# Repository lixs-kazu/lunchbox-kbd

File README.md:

# lunchbox-kbd　egg52で不満だった部分を変更したキーボード

具体的には

・使用頻度が極めて低かったため、小指の外側の一列を削除

・できるだけ指の移動量がを減らすため、縦のキーピッチを１８mmに変更。そのため通常のキーキャップは使用できない可能性がある（キーキャップを削る事によって使用可能）chocスイッチの場合問題なく使用できる。

・親指を使用した入力時、他のキーに手が当たるのを防ぐ為に親指部分の角度を変更。

・親指部分の４キーを内側に２mm移動。

・人差し指部分のキーが押しにくかったため、中指から6.5mmの差をつけた。

・小指部分のキーも同様だったので、中指から20mmの差をつけた。

・アクリル箱組ケース制作するときに可能な限りサイドパネルの枚数を減らしたいので、外形を五角形とした。

・ケーブル横出しは狭いスペースで作業するときに邪魔になるので上側にケーブルがでるように変更。

・LEDとOLEDに対応。

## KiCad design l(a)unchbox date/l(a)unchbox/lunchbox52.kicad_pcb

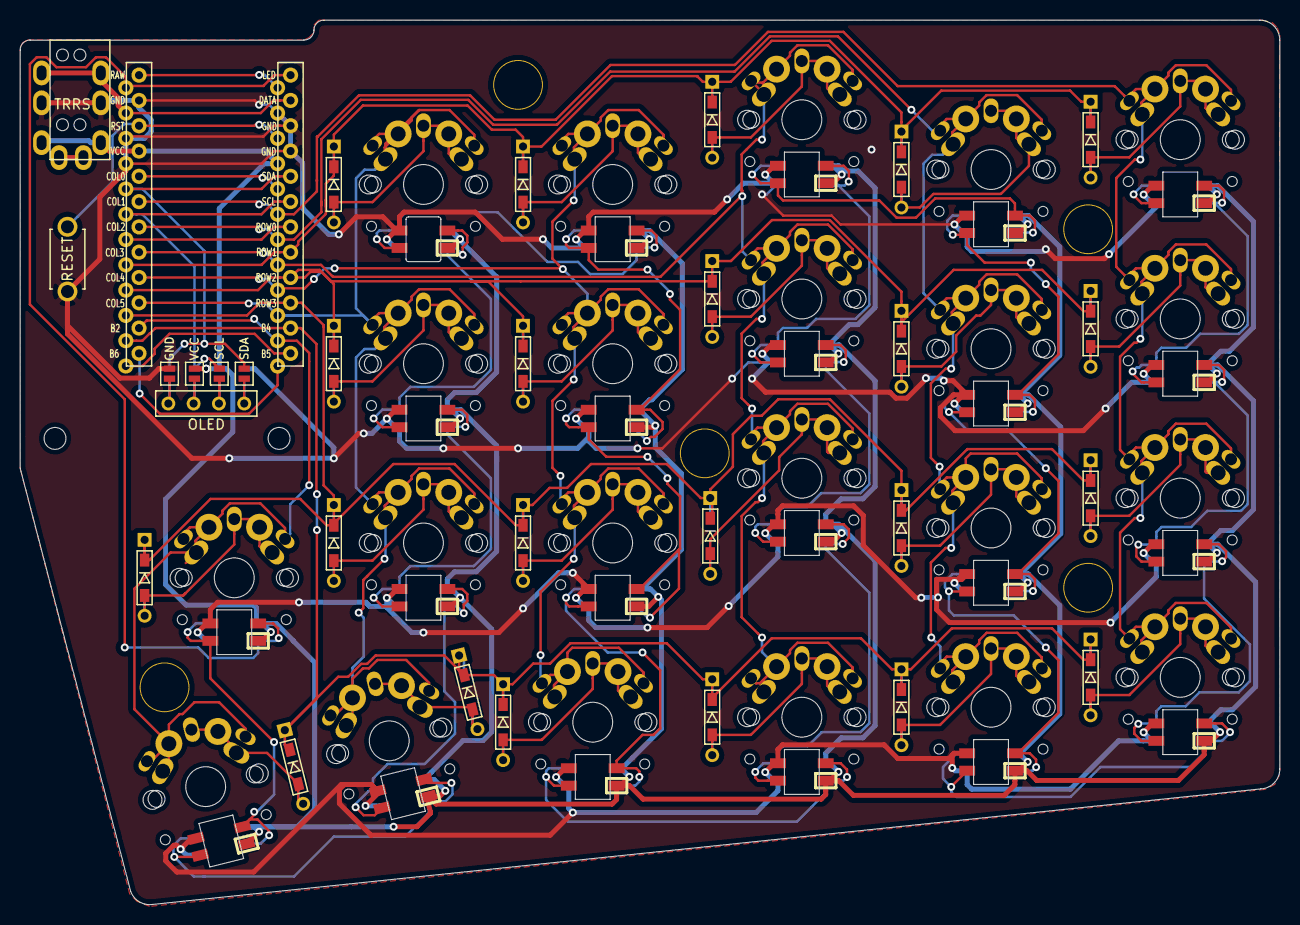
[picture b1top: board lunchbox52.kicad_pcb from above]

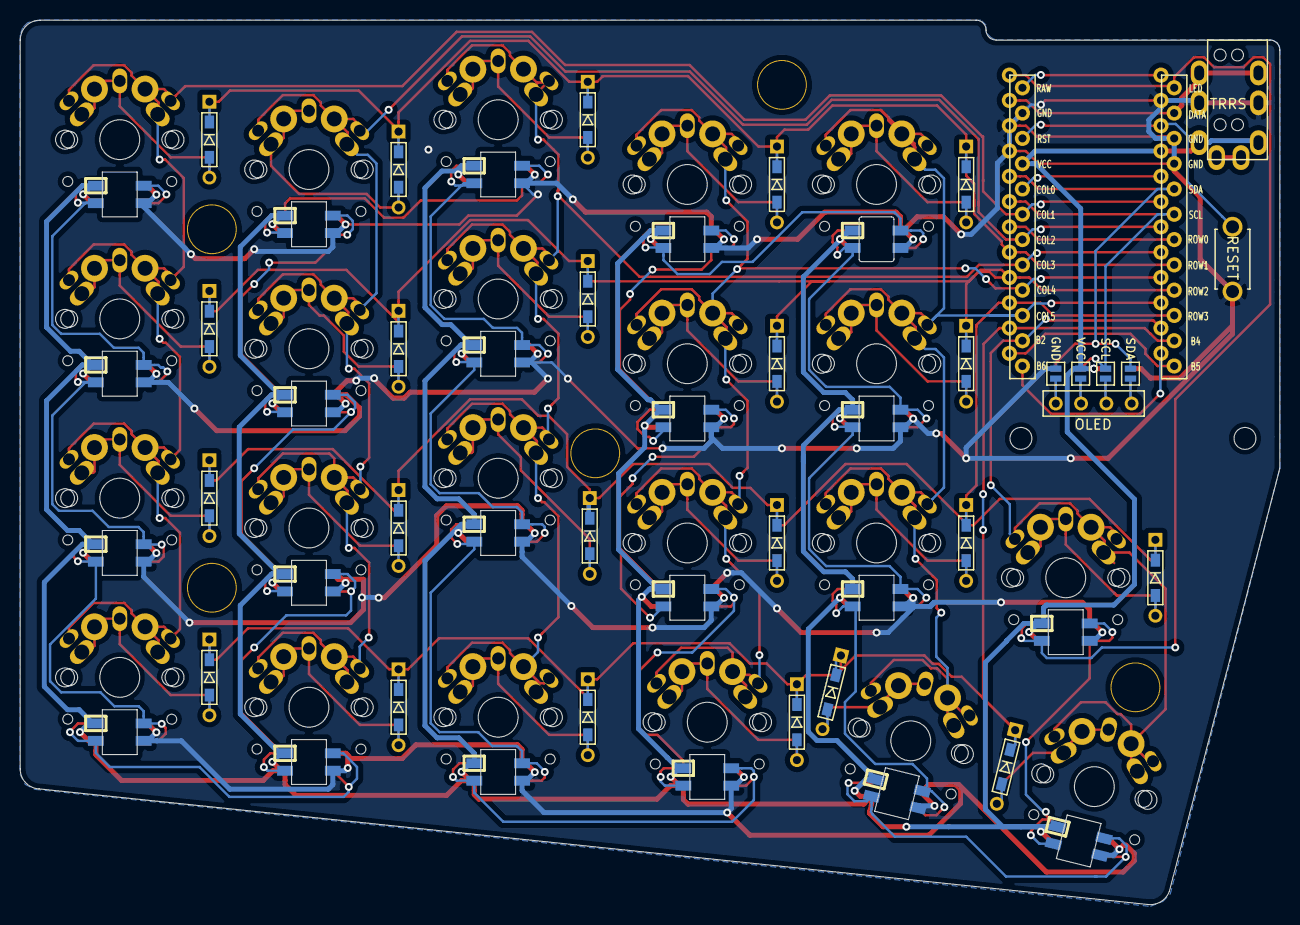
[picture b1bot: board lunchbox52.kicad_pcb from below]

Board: 2 copper layers, 126.5 x 88.8 mm, 83 parts (4 on the bottom side), 64 nets.

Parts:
D1, D2, D3, D4, D5, D6, D7, D8, D9, D10, D11, D12, D13, D14, D15, D16, D17, D18, D19, D20, D21, D22: D; D3_TH_SMD
J1: MJ-4PP-9
J2: Conn_01x04_Female; OLED
JP1, JP8: GND; Jumper
JP2, JP7: VCC; Jumper
JP3, JP6: SCL; Jumper
JP4, JP5: SDA; Jumper
L1, L2, L3, L4, L5, L6, L7, L8, L9, L10, L11, L12, L13, L14, L15, L16, L17, L18, L19, L20, L21, L22: SK6812MINI; SK6812MINI_rev
Ref**: Val**; HOLE
Ref**#2, Ref**#3, Ref**#4, Ref**#5: Val**; HOLE
SW1: SW_PUSH; ResetSW
SW2, SW3, SW4, SW5, SW6, SW7, SW8, SW9, SW10, SW11, SW12, SW13, SW14, SW15, SW16, SW17, SW18, SW19, SW20, SW21, SW22, SW23: SW_Push; MX_PG1350_FLIP_HOLES
U1: ProMicro; ProMicro_v2

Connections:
GND: J1.C, JP1.2, JP8.2, L1.2, L2.2, L3.2, L4.2, L5.2, L6.2, L7.2, L8.2, L9.2, L10.2, L11.2, L12.2, L13.2, L14.2, L15.2, L16.2, L17.2, L18.2, L19.2, L20.2, L21.2, L22.2, SW1.2, U1.3, U1.4, U1.23
LED: L1.3, U1.1
unnamed: D1.2, SW2.2
unnamed: D2.2, SW3.2
unnamed: D3.2, SW4.2
unnamed: D4.2, SW5.2
unnamed: D5.2, SW6.2
unnamed: D6.2, SW7.2
unnamed: D7.2, SW8.2
unnamed: D8.2, SW9.2
unnamed: D9.2, SW10.2
unnamed: D10.2, SW11.2
unnamed: D11.2, SW12.2
unnamed: D12.2, SW13.2
unnamed: D13.2, SW14.2
unnamed: D14.2, SW15.2
unnamed: D15.2, SW16.2
unnamed: D16.2, SW17.2
unnamed: D17.2, SW18.2
unnamed: D18.2, SW19.2
unnamed: D19.2, SW20.2
unnamed: D20.2, SW21.2
unnamed: D21.2, SW22.2
unnamed: D22.2, SW23.2
unnamed: J2.1, JP4.1, JP8.1
unnamed: J2.2, JP3.1, JP7.1
unnamed: J2.3, JP2.1, JP6.1
unnamed: J2.4, JP1.1, JP5.1
unnamed: L1.1, L2.3
unnamed: L2.1, L6.3
unnamed: L3.1, L7.3
unnamed: L3.3, L4.1
unnamed: L4.3, L5.1
unnamed: L5.3, L6.1
unnamed: L7.1, L8.3
unnamed: L8.1, L9.3
unnamed: L10.1, L14.3
unnamed: L9.1, L10.3
unnamed: L11.1, L15.3
unnamed: L11.3, L12.1
unnamed: L12.3, L13.1
unnamed: L13.3, L14.1
unnamed: L15.1, L16.3
unnamed: L16.1, L17.3
unnamed: L17.1, L18.3
unnamed: L18.1, L22.3
unnamed: L19.3, L20.1
unnamed: L20.3, L21.1
unnamed: L21.3, L22.1
RST: SW1.1, U1.22
SCL: JP3.2, JP6.2, U1.6
SDA: JP4.2, JP5.2, U1.5
VCC: J1.D, JP2.2, JP7.2, L1.4, L2.4, L3.4, L4.4, L5.4, L6.4, L7.4, L8.4, L9.4, L10.4, L11.4, L12.4, L13.4, L14.4, L15.4, L16.4, L17.4, L18.4, L19.4, L20.4, L21.4, L22.4, U1.21
col1: SW20.1, SW21.1, SW22.1, SW23.1, U1.19
col2: SW16.1, SW17.1, SW18.1, SW19.1, U1.18
col3: SW12.1, SW13.1, SW14.1, SW15.1, U1.17
col4: SW8.1, SW9.1, SW10.1, SW11.1, U1.16
col5: SW4.1, SW5.1, SW6.1, SW7.1, U1.15
col6: SW2.1, SW3.1, U1.14
date: J1.B, U1.2
row1: D3.1, D7.1, D11.1, D15.1, D19.1, U1.8
row2: D4.1, D8.1, D12.1, D16.1, D20.1, U1.9
row3: D1.1, D5.1, D9.1, D13.1, D17.1, D21.1, U1.10
row4: D2.1, D6.1, D10.1, D14.1, D18.1, D22.1, U1.11

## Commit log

2019-06-17 Create pcb
